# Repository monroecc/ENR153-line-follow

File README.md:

A simple arduino sketch to control a car (car.jpg) as it drives around a track.

control_board
--------------
Contains control board schematic files, parts list, users manual, and LaTex source files.

pid_info
--------
Contains a basic introduction to PID control and PID tuning instructions. This is a good starting point for anyone wanting to tune the PID values if the current ones aren't working out.

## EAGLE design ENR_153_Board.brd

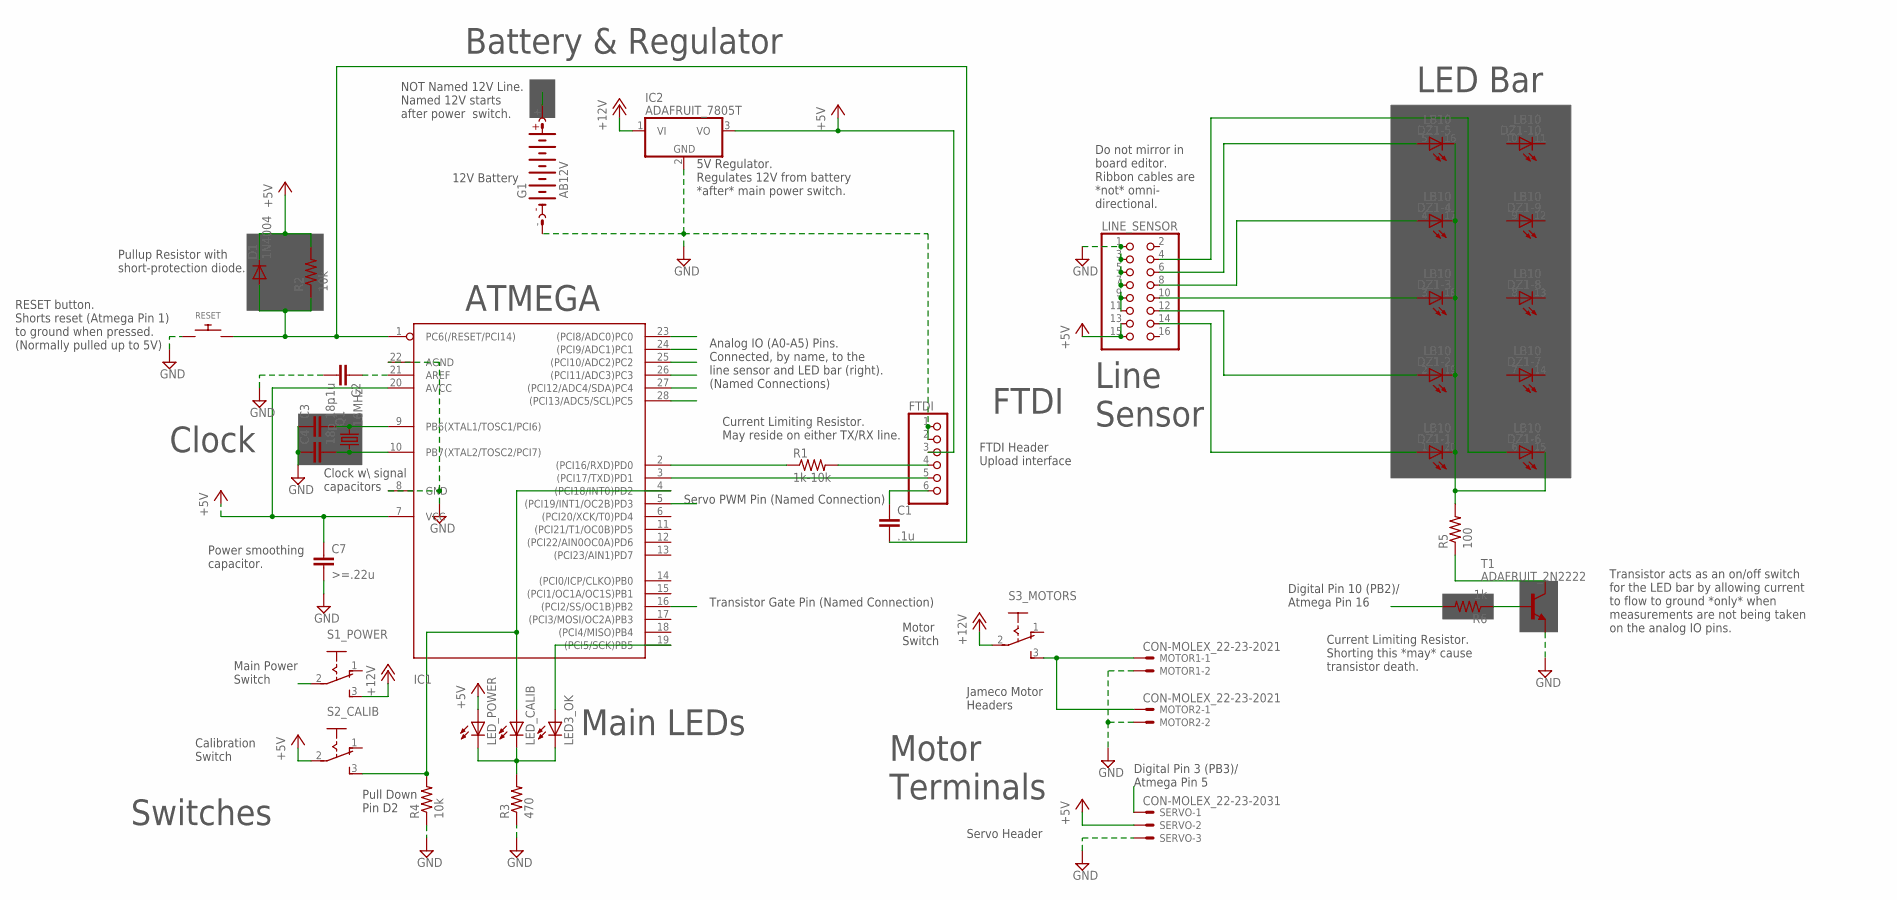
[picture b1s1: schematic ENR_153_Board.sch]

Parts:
C1, C2: .1u; CAPACITOR-WIMA_C5B3
C3, C4: 18p; CAPACITOR-WIMA_C5B3
C7: >=.22u; CAPACITOR-WIMA_C5B3
D1: 1N4004; DIODE_DO35-7
DZ1: LB10
FTDI: PINHD-1X6; 1X06
G1: AB12V; BATTERY_AB9V
IC1: ATMEGA168V-10P; DIL28-3
IC2: ADAFRUIT_7805T; ADAFRUIT_TO220H
LED3_OK: ADAFRUIT_LEDSQR2X5; ADAFRUIT_LED2X5
LED_CALIB: ADAFRUIT_LEDSQR2X5; ADAFRUIT_LED2X5
LED_POWER: ADAFRUIT_LEDSQR2X5; ADAFRUIT_LED2X5
LINE_SENSOR: PINHEAD_PINHD-2X8; PINHEAD_2X08
MOTOR1, MOTOR2: CON-MOLEX_22-23-2021
Q1: 16MHz; ADAFRUIT_HC49/S
R1: 1k-10k; ADAFRUIT_0207/7
R2, R4: 10k; ADAFRUIT_0207/7
R3: 470; ADAFRUIT_0207/7
R5: 100; ADAFRUIT_0207/7
R6: 1k; ADAFRUIT_0207/7
RESET: ADAFRUIT_SWITCH_PUSHBUTTONEVQ-PE; ADAFRUIT_TACT_PANA-EVQ
S1_POWER, S2_CALIB, S3_MOTORS: SWITCH_255SB
SERVO: CON-MOLEX_22-23-2031
T1: ADAFRUIT_2N2222; ADAFRUIT_TO92-EBC-OVAL

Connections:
+5V: C7.1, D1.C, FTDI.3, IC1.7 (VCC), IC1.20 (AVCC), IC2.3 (VO), LED_POWER.A, LINE_SENSOR.13, LINE_SENSOR.15, R2.2, S2_CALIB.2, SERVO.2
+12V: IC2.1 (VI), S1_POWER.3 (S), S3_MOTORS.2
A0: DZ1.6 (A), IC1.23 ((PCI8/ADC0)PC0), LINE_SENSOR.4
A1: DZ1.5 (A), IC1.24 ((PCI9/ADC1)PC1), LINE_SENSOR.6
A2: DZ1.4 (A), IC1.25 ((PCI10/ADC2)PC2), LINE_SENSOR.8
A3: DZ1.3 (A), IC1.26 ((PCI11/ADC3)PC3), LINE_SENSOR.10
A4: DZ1.2 (A), IC1.27 ((PCI12/ADC4/SDA)PC4), LINE_SENSOR.12
A5: DZ1.1 (A), IC1.28 ((PCI13/ADC5/SCL)PC5), LINE_SENSOR.14
GND: C2.2, C3.1, C4.1, C7.2, FTDI.1, FTDI.2, G1.-, IC1.8 (GND), IC1.22 (AGND), IC2.2 (GND), LINE_SENSOR.1, LINE_SENSOR.3, LINE_SENSOR.5, LINE_SENSOR.7, LINE_SENSOR.9, LINE_SENSOR.11, MOTOR1.2, MOTOR2.2, R3.1, R4.1, RESET.P$1, SERVO.3, T1.E
MAINS: G1.+, S1_POWER.2
unnamed: C1.2, D1.A, IC1.1 (PC6(/RESET/PCI14)), R2.1, RESET.P$2
unnamed: R5.1, T1.C
unnamed: FTDI.4, R1.2
unnamed: C1.1, FTDI.6
unnamed: IC1.2 ((PCI16/RXD)PD0), R1.1
unnamed: FTDI.5, IC1.3 ((PCI17/TXD)PD1)
unnamed: C2.1, IC1.21 (AREF)
unnamed: IC1.19 ((PCI5/SCK)PB5), LED3_OK.A
unnamed: LED3_OK.K (C), LED_CALIB.K (C), LED_POWER.K (C), R3.2
unnamed: C3.2, IC1.9 (PB6(XTAL1/TOSC1/PCI6)), Q1.2
unnamed: C4.2, IC1.10 (PB7(XTAL2/TOSC2/PCI7)), Q1.1
unnamed: R6.1, T1.B
unnamed: DZ1.15 (C), DZ1.16 (C), DZ1.17 (C), DZ1.18 (C), DZ1.19 (C), DZ1.20 (C), R5.2
unnamed: IC1.4 ((PCI18/INT0)PD2), LED_CALIB.A, R4.2, S2_CALIB.3 (S)
unnamed: MOTOR1.1, MOTOR2.1, S3_MOTORS.3 (S)
SERVO: IC1.5 ((PCI19/INT1/OC2B)PD3), SERVO.1
TRANSISTOR_GATE: IC1.16 ((PCI2/SS/OC1B)PB2), R6.2

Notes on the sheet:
Current Limiting Resistor. May reside on either TX/RX line.
Analog IO (A0-A5) Pins. Connected, by name, to the line sensor and LED bar (right). (Named Connections)
5V Regulator. Regulates 12V from battery *after* main power switch.
Servo Header
Jameco Motor Headers
Main Power Switch
Motor Switch
Calibration Switch
Pull Down Pin D2
LED Bar
ATMEGA
FTDI Header Upload interface
12V Battery
NOT Named 12V Line. Named 12V starts after power switch.
Power smoothing capacitor.
Current Limiting Resistor. Shorting this *may* cause transistor death.
Transistor acts as an on/off switch for the LED bar by allowing current to flow to ground *only* when measurements are not being taken on the analog IO pins.
Do not mirror in board editor. Ribbon cables are *not* omni- directional.
Digital Pin 10 (PB2)/ Atmega Pin 16
Transistor Gate Pin (Named Connection)
Servo PWM Pin (Named Connection)
Digital Pin 3 (PB3)/ Atmega Pin 5
Clock w\ signal capacitors
Pullup Resistor with short-protection diode.
RESET button. Shorts reset (Atmega Pin 1) to ground when pressed. (Normally pulled up to 5V)
Clock
Main LEDs
Switches
Line Sensor
Battery & Regulator
FTDI
Motor Terminals

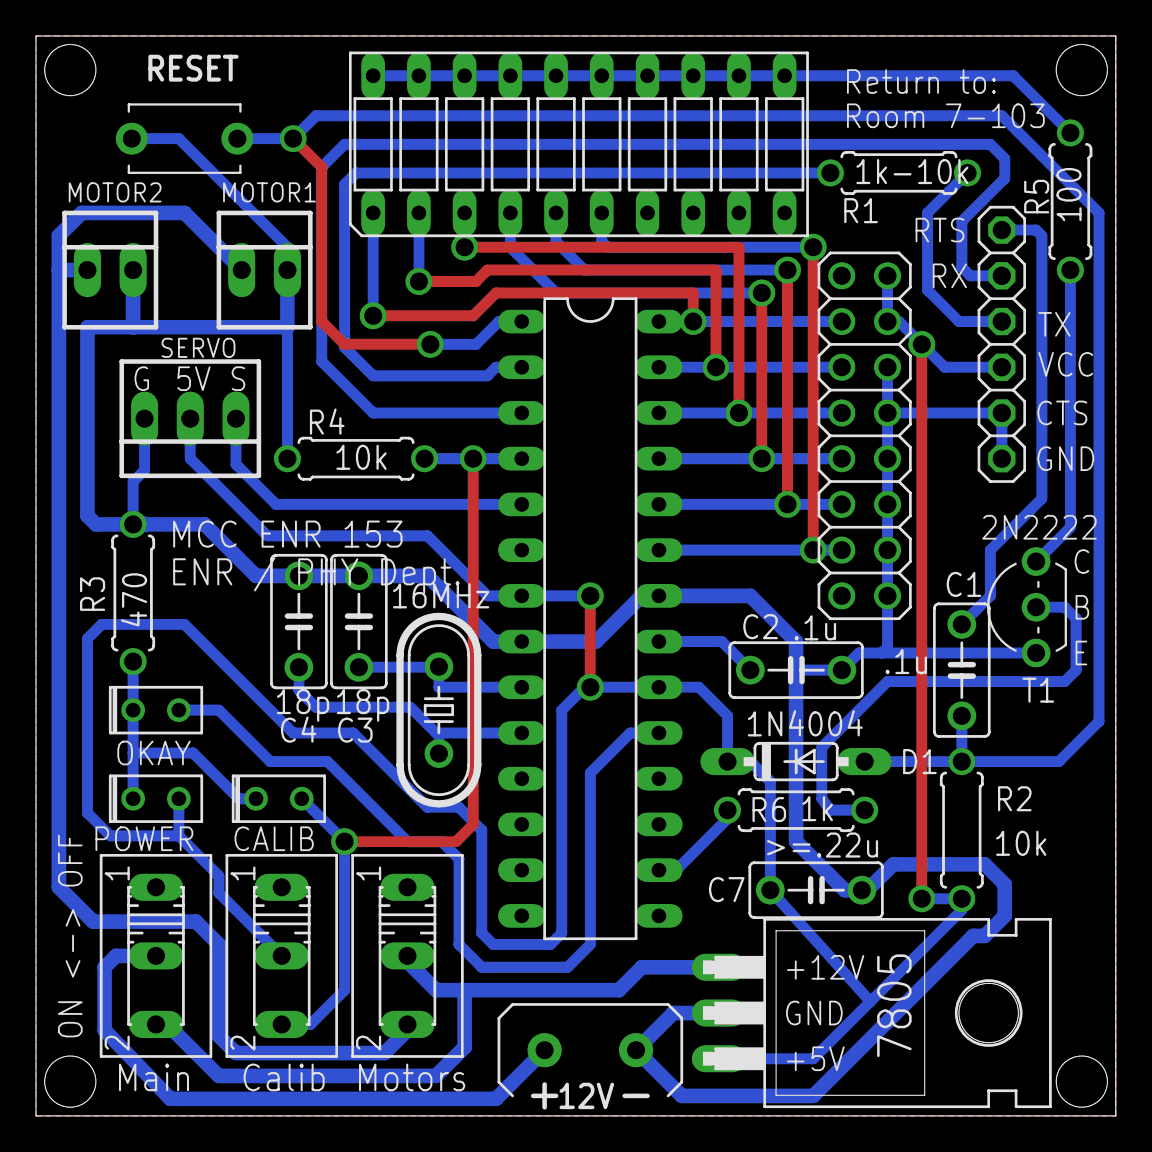
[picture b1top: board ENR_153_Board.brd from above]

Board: 2 copper layers, 60.0 x 60.0 mm, 30 parts (0 on the bottom side), 27 nets.

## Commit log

2016-07-19 inital commit
2016-07-19 fixed readme
2016-07-28 works, pid needs tuning
2016-07-29 tuned PID, added definitions file
2016-08-01 made read_line faster
2016-08-02 fixed bug
2016-08-09 tuned line follow, removed unessisary code
2016-08-10 changed how integral is evaluated
2016-08-10 did weirds stuff with i term
2016-08-11 Added Eagle files
2016-08-12 added pdf's for pid, more comments
2016-08-12 added parts list, manual, and latex source (zip)
2016-08-12 Added Finalized Board and Schematic Files.
2016-12-05 Low pass filter on Integeral term of PID removed
